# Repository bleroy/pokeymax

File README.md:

# This repo is somewhat obsolete

I created this repo when Foft first released his design of the PokeyMax 4 board publicly.
I did so at the time because the design was still in Eagle format and somewhat difficult to keep track of.
I took the design, imported it to KiCad and published it here as a git repo.
I also took a stab at redesigning the board to bring the price down as much as possible (that's the 4s version of the board).

A lot has happened since.
Foft released multiple revisions of the board and HDL files, and quite a few people have built their own boards.
He's now using KiCad, so no more Eagle.
He also started working on a 4.5 revision as well as on several new designs, including the PokeyMin that uses a smaller FPGA version and resistors instead of level shifters.
That last design pretty much makes 4s obsolete and little more than a curiosity. For me, it was a nice exercise in designing such a small board.

In other words, nobody except maybe me should use the files on this repo. Instead, head over to Foft's site and download the latest files from there:
http://www.64kib.com/atarixlfpga_svn/trunk/atari_800xl/atari_chips/hardware/

# PokeyMax 4

Foft's public designs for PokeyMax.

Pokeys are getting rare and expensive. FPGA alternatives exist but are also expensive. Foft, the author of PokeyMax, has very generously made his designs public on [the AtariAge forums](https://forums.atariage.com/topic/364870-pokeymax-v4-bring-up-thread/).
With his permission, I'm publishing his latest iteration on PokeyMax, version 4, which is a 2-layer version with all components on the top side. This should be easier to produce at a lower cost than the previous versions. I've also imported the project in KiCad from the original Eagle files.

Foft has not specified a license for his work, but attribution should be maintained. This is his design, reproduced here under his permission.

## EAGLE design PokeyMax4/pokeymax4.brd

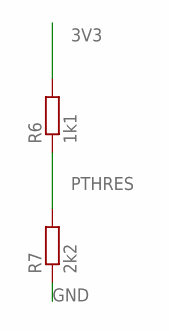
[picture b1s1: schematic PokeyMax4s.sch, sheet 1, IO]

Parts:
R6: 1k1; R0402
R7: 2k2; R0402

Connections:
3V3: R6.2; also elsewhere on the board
GND: R7.1; also elsewhere on the board
PTHRES: R6.1, R7.2; also elsewhere on the board

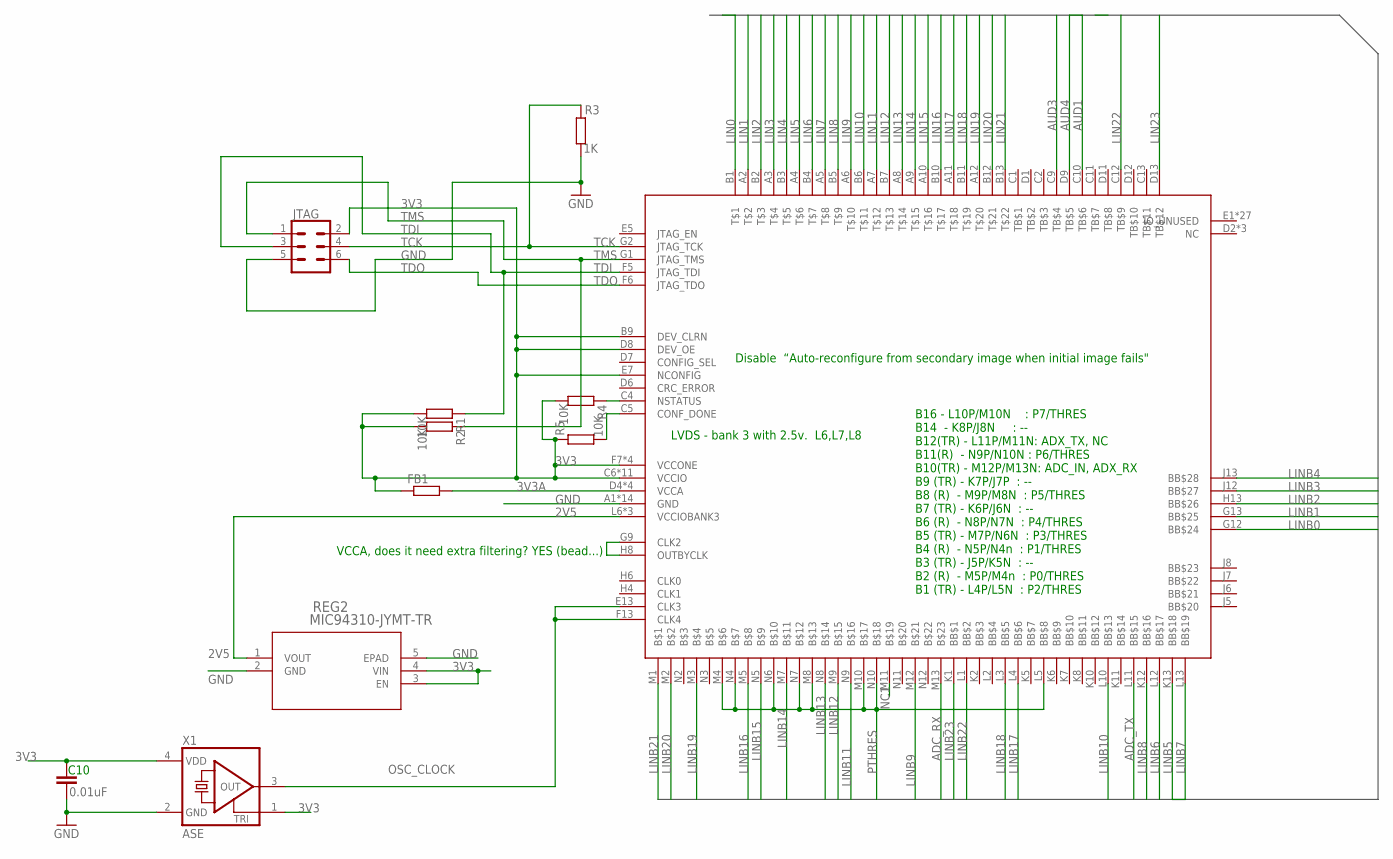
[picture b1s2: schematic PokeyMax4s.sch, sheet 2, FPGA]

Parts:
C10: 0.01uF; C0402
FB1: R-EU_R0402; R0402
JTAG: CONN_03X2LOCK; 2X3_LOCK
R1, R2, R4, R5: 10K; R0402
R3: 1K; R0402
REG2: MIC94310-JYMT-TR; TDFN4_1P2X1P6_MCH
U3: MAX10; U169SMALL
X1: ASE

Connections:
2V5: REG2.1 (VOUT), U3.L6 (VCCIOBANK3), U3.L7 (VCCIOBANK3), U3.L8 (VCCIOBANK3); also elsewhere on the board
3V3: C10.1, FB1.1, JTAG.2, R1.2, R2.2, R4.2, R5.1, REG2.3 (EN), REG2.4 (VIN), U3.B9 (DEV_CLRN), U3.C6 (VCCIO), U3.C7 (VCCIO), U3.C8 (VCCIO), U3.D8 (DEV_OE), U3.E7 (NCONFIG), U3.F2 (VCCIO), U3.F7 (VCCONE), U3.F11 (VCCIO), U3.G3 (VCCIO), U3.G6 (VCCONE), U3.G8 (VCCONE), U3.G11 (VCCIO), U3.H7 (VCCONE), U3.H11 (VCCIO), U3.J3 (VCCIO), U3.J11 (VCCIO), U3.K3 (VCCIO), X1.1 (TRI), X1.4 (VDD); also elsewhere on the board
3V3A: FB1.2, U3.D4 (VCCA), U3.D10 (VCCA), U3.K4 (VCCA), U3.K9 (VCCA); also elsewhere on the board
ADC_RX: U3.M13; also elsewhere on the board
ADC_TX: U3.L11 (BB$15); also elsewhere on the board
AUD1: U3.C10 (TB$6); also elsewhere on the board
AUD3: U3.C9 (TB$4); also elsewhere on the board
AUD4: U3.D9 (TB$5); also elsewhere on the board
CONF_DONE: R5.2, U3.C5 (CONF_DONE)
FAKE_CLK: U3.G9 (CLK2), U3.H8 (OUTBYCLK)
GND: C10.2, JTAG.5, R3.2, REG2.2 (GND), REG2.5 (EPAD), U3.A1 (GND), U3.A13 (GND), U3.B8 (GND), U3.C3 (GND), U3.D5 (GND), U3.E11 (GND), U3.F3 (GND), U3.G7 (GND), U3.H12 (GND), U3.J4 (GND), U3.L9 (GND), U3.M6 (GND), U3.N1 (GND), U3.N13 (GND), X1.2 (GND); also elsewhere on the board
LIN0: U3.B1; also elsewhere on the board
LIN1: U3.A2; also elsewhere on the board
LIN2: U3.B2; also elsewhere on the board
LIN3: U3.A3; also elsewhere on the board
LIN4: U3.B3; also elsewhere on the board
LIN5: U3.A4; also elsewhere on the board
LIN6: U3.B4; also elsewhere on the board
LIN7: U3.A5; also elsewhere on the board
LIN8: U3.B5; also elsewhere on the board
LIN9: U3.A6; also elsewhere on the board
LIN10: U3.B6; also elsewhere on the board
LIN11: U3.A7; also elsewhere on the board
LIN12: U3.B7; also elsewhere on the board
LIN13: U3.A8; also elsewhere on the board
LIN14: U3.A9; also elsewhere on the board
LIN15: U3.A10; also elsewhere on the board
LIN16: U3.B10; also elsewhere on the board
LIN17: U3.A11; also elsewhere on the board
LIN18: U3.B11; also elsewhere on the board
LIN19: U3.A12; also elsewhere on the board
LIN20: U3.B12; also elsewhere on the board
LIN21: U3.B13; also elsewhere on the board
LIN22: U3.C12 (TB$9); also elsewhere on the board
LIN23: U3.D13 (TB$12); also elsewhere on the board
LINB0: U3.G12 (BB$24); also elsewhere on the board
LINB1: U3.G13 (BB$25); also elsewhere on the board
LINB2: U3.H13 (BB$26); also elsewhere on the board
LINB3: U3.J12 (BB$27); also elsewhere on the board
LINB4: U3.J13 (BB$28); also elsewhere on the board
LINB5: U3.K13 (BB$18); also elsewhere on the board
LINB6: U3.L12 (BB$17); also elsewhere on the board
LINB7: U3.L13 (BB$19); also elsewhere on the board
LINB8: U3.K12 (BB$16); also elsewhere on the board
LINB9: U3.M12; also elsewhere on the board
LINB10: U3.L10 (BB$13); also elsewhere on the board
LINB11: U3.N9; also elsewhere on the board
LINB12: U3.M9; also elsewhere on the board
LINB13: U3.N8; also elsewhere on the board
LINB14: U3.M7; also elsewhere on the board
LINB15: U3.N5; also elsewhere on the board
LINB16: U3.M5; also elsewhere on the board
LINB17: U3.L4 (BB$6); also elsewhere on the board
LINB18: U3.L3 (BB$5); also elsewhere on the board
LINB19: U3.M3; also elsewhere on the board
LINB20: U3.M2; also elsewhere on the board
LINB21: U3.M1; also elsewhere on the board
LINB22: U3.L1 (BB$2); also elsewhere on the board
LINB23: U3.K1 (BB$1); also elsewhere on the board
NC1: U3.M11
NSTATUS: R4.1, U3.C4 (NSTATUS)
OSC_CLOCK: U3.E13 (CLK3), U3.F13 (CLK4), X1.3 (OUT)
PTHRES: U3.L5 (BB$8), U3.M4, U3.M8, U3.M10, U3.N4, U3.N6, U3.N7, U3.N10; also elsewhere on the board
TCK: JTAG.4, R3.1, U3.G2 (JTAG_TCK)
TDI: JTAG.3, R1.1, U3.F5 (JTAG_TDI)
TDO: JTAG.6, U3.F6 (JTAG_TDO)
TMS: JTAG.1, R2.1, U3.G1 (JTAG_TMS)

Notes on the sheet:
VCCA, does it need extra filtering? YES (bead...)
Disable “Auto-reconfigure from secondary image when initial image fails"
LVDS - bank 3 with 2.5v. L6,L7,L8
B16 - L10P/M10N : P7/THRES B14 - K8P/J8N : -- B12(TR) - L11P/M11N: ADX_TX, NC B11(R) - N9P/N10N : P6/THRES B10(TR) - M12P/M13N: ADC_IN, ADX_RX B9 (TR) - K7P/J7P : -- B8 (R) - M9P/M8N : P5/THRES B7 (TR) - K6P/J6N : -- B6 (R) - N8P/N7N : P4/THRES B5 (TR) - M7P/N6N : P3/THRES B4 (R) - N5P/N4n : P1/THR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

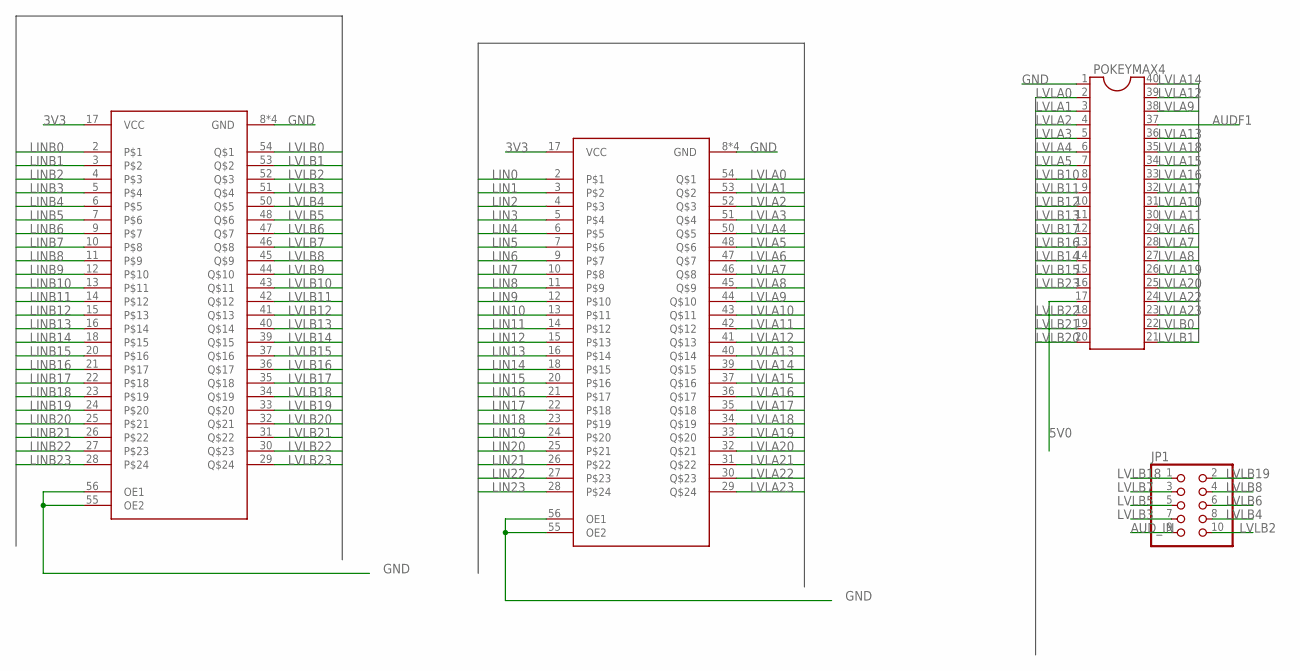
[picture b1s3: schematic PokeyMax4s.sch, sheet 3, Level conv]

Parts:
JP1: PINHD-2X5; 2X05
POKEYMAX4: DIL40
U2, U4: SN74CB3T16211SM; 56TVSOP_SMALL

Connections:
3V3: U2.17 (VCC), U4.17 (VCC); also elsewhere on the board
5V0: POKEYMAX4.17; also elsewhere on the board
AUDF1: POKEYMAX4.37; also elsewhere on the board
AUD_IN: JP1.9; also elsewhere on the board
GND: POKEYMAX4.1, U2.8 (GND), U2.19 (GND), U2.38 (GND), U2.49 (GND), U2.55 (OE2), U2.56 (OE1), U4.8 (GND), U4.19 (GND), U4.38 (GND), U4.49 (GND), U4.55 (OE2), U4.56 (OE1); also elsewhere on the board
LIN0: U2.2; also elsewhere on the board
LIN1: U2.3; also elsewhere on the board
LIN2: U2.4; also elsewhere on the board
LIN3: U2.5; also elsewhere on the board
LIN4: U2.6; also elsewhere on the board
LIN5: U2.7; also elsewhere on the board
LIN6: U2.9; also elsewhere on the board
LIN7: U2.10; also elsewhere on the board
LIN8: U2.11; also elsewhere on the board
LIN9: U2.12; also elsewhere on the board
LIN10: U2.13; also elsewhere on the board
LIN11: U2.14; also elsewhere on the board
LIN12: U2.15; also elsewhere on the board
LIN13: U2.16; also elsewhere on the board
LIN14: U2.18; also elsewhere on the board
LIN15: U2.20; also elsewhere on the board
LIN16: U2.21; also elsewhere on the board
LIN17: U2.22; also elsewhere on the board
LIN18: U2.23; also elsewhere on the board
LIN19: U2.24; also elsewhere on the board
LIN20: U2.25; also elsewhere on the board
LIN21: U2.26; also elsewhere on the board
LIN22: U2.27; also elsewhere on the board
LIN23: U2.28; also elsewhere on the board
LINB0: U4.2; also elsewhere on the board
LINB1: U4.3; also elsewhere on the board
LINB2: U4.4; also elsewhere on the board
LINB3: U4.5; also elsewhere on the board
LINB4: U4.6; also elsewhere on the board
LINB5: U4.7; also elsewhere on the board
LINB6: U4.9; also elsewhere on the board
LINB7: U4.10; also elsewhere on the board
LINB8: U4.11; also elsewhere on the board
LINB9: U4.12; also elsewhere on the board
LINB10: U4.13; also elsewhere on the board
LINB11: U4.14; also elsewhere on the board
LINB12: U4.15; also elsewhere on the board
LINB13: U4.16; also elsewhere on the board
LINB14: U4.18; also elsewhere on the board
LINB15: U4.20; also elsewhere on the board
LINB16: U4.21; also elsewhere on the board
LINB17: U4.22; also elsewhere on the board
LINB18: U4.23; also elsewhere on the board
LINB19: U4.24; also elsewhere on the board
LINB20: U4.25; also elsewhere on the board
LINB21: U4.26; also elsewhere on the board
LINB22: U4.27; also elsewhere on the board
LINB23: U4.28; also elsewhere on the board
LVLA0: POKEYMAX4.2, U2.54
LVLA1: POKEYMAX4.3, U2.53
LVLA2: POKEYMAX4.4, U2.52
LVLA3: POKEYMAX4.5, U2.51
LVLA4: POKEYMAX4.6, U2.50
LVLA5: POKEYMAX4.7, U2.48
LVLA6: POKEYMAX4.29, U2.47
LVLA7: POKEYMAX4.28, U2.46
LVLA8: POKEYMAX4.27, U2.45
LVLA9: POKEYMAX4.38, U2.44
LVLA10: POKEYMAX4.31, U2.43
LVLA11: POKEYMAX4.30, U2.42
LVLA12: POKEYMAX4.39, U2.41
LVLA13: POKEYMAX4.36, U2.40
LVLA14: POKEYMAX4.40, U2.39
LVLA15: POKEYMAX4.34, U2.37
LVLA16: POKEYMAX4.33, U2.36
LVLA17: POKEYMAX4.32, U2.35
LVLA18: POKEYMAX4.35, U2.34
LVLA19: POKEYMAX4.26, U2.33
LVLA20: POKEYMAX4.25, U2.32
LVLA21: U2.31; also elsewhere on the board
LVLA22: POKEYMAX4.24, U2.30
LVLA23: POKEYMAX4.23, U2.29
LVLB0: POKEYMAX4.22, U4.54
LVLB1: POKEYMAX4.21, U4.53
LVLB2: JP1.10, U4.52
LVLB3: JP1.7, U4.51
LVLB4: JP1.8, U4.50
LVLB5: JP1.5, U4.48
LVLB6: JP1.6, U4.47
LVLB7: JP1.3, U4.46
LVLB8: JP1.4, U4.45
LVLB9: U4.44; also elsewhere on the board
LVLB10: POKEYMAX4.8, U4.43
LVLB11: POKEYMAX4.9, U4.42
LVLB12: POKEYMAX4.10, U4.41
LVLB13: POKEYMAX4.11, U4.40
LVLB14: POKEYMAX4.14, U4.39
LVLB15: POKEYMAX4.15, U4.37
LVLB16: POKEYMAX4.13, U4.36
LVLB17: POKEYMAX4.12, U4.35
LVLB18: JP1.1, U4.34
LVLB19: JP1.2, U4.33
LVLB20: POKEYMAX4.20, U4.32
LVLB21: POKEYMAX4.19, U4.31
LVLB22: POKEYMAX4.18, U4.30
LVLB23: POKEYMAX4.16, U4.29

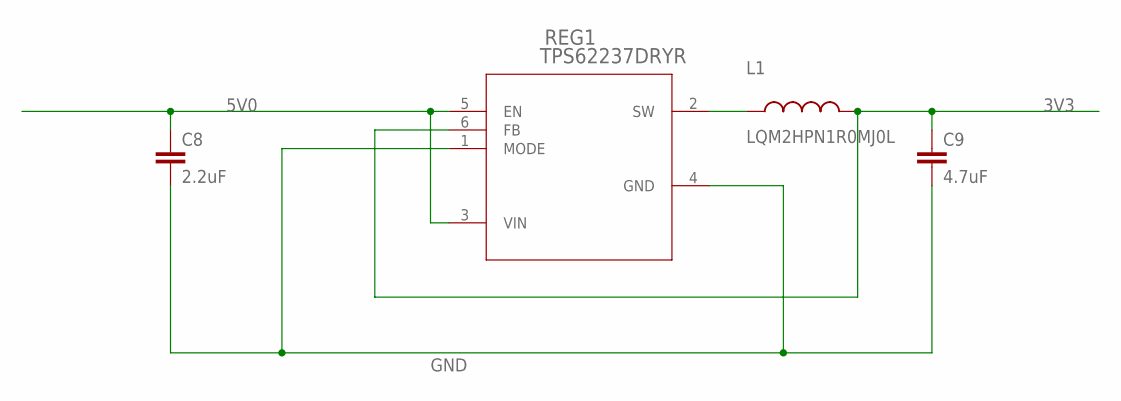
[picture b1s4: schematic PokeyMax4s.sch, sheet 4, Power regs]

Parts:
C8: 2.2uF; C0402
C9: 4.7uF; C0402
L1: LQM2HPN1R0MJ0L; INDC1008X04
REG1: TPS62237DRYR; DRY6

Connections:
3V3: C9.1, L1.2, REG1.6 (FB); also elsewhere on the board
5V0: C8.1, REG1.3 (VIN), REG1.5 (EN); also elsewhere on the board
GND: C8.2, C9.2, REG1.1 (MODE), REG1.4 (GND); also elsewhere on the board
unnamed: L1.1, REG1.2 (SW)

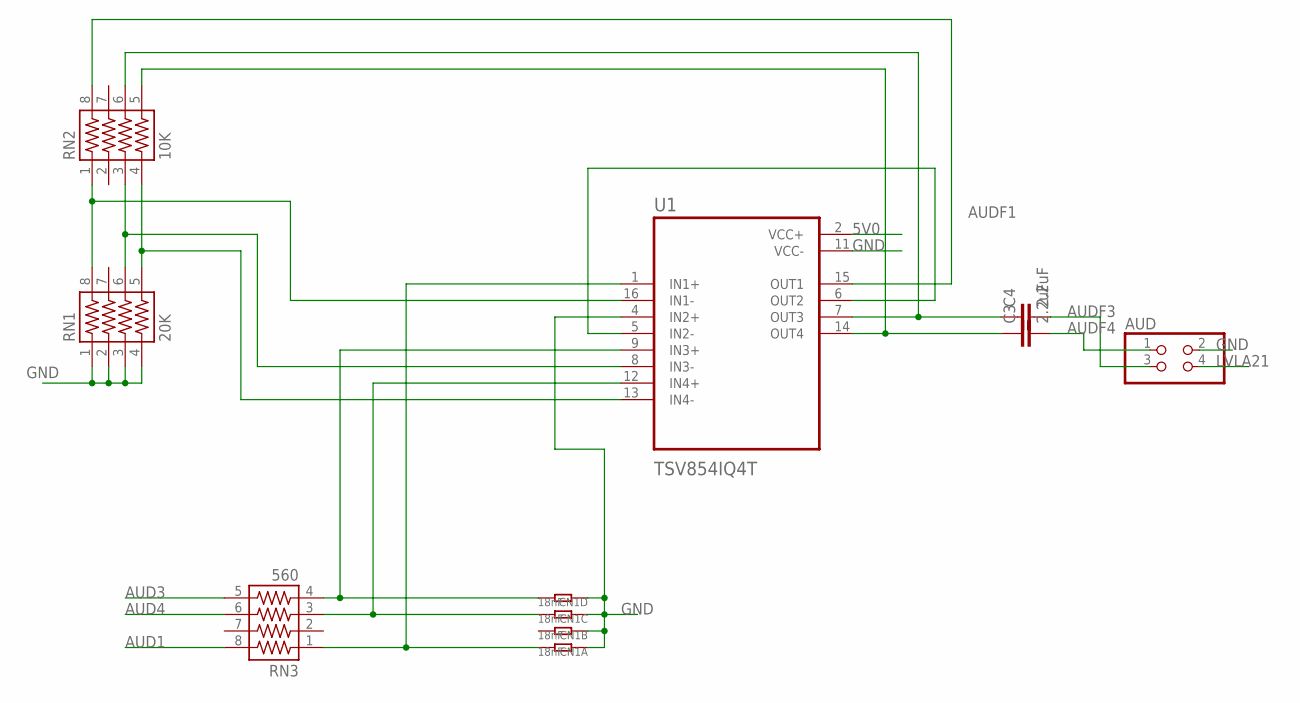
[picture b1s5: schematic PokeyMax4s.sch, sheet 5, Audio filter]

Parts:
AUD: PINHD-2X2; 2X02
C3, C4: 2.2uF; C0402
CN1: 18nF; R1206-8
RN1: 20K; 741-8
RN2: 10K; 741-8
RN3: 560; 741-8
U1: TSV854IQ4T; QFN50P300X300X100-16N

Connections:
5V0: U1.2 (VCC+); also elsewhere on the board
AMPIN1M: RN1.8, RN2.1, U1.16 (IN1-)
AMPIN1P: CN1.8 (2), RN3.1, U1.1 (IN1+)
AMPIN3M: RN1.6, RN2.3, U1.8 (IN3-)
AMPIN3P: CN1.5 (2), RN3.4, U1.9 (IN3+)
AMPIN4P: CN1.6 (2), RN3.3, U1.12 (IN4+)
AUD1: RN3.8; also elsewhere on the board
AUD3: RN3.5; also elsewhere on the board
AUD4: RN3.6; also elsewhere on the board
AUDF1: RN2.8, U1.15 (OUT1); also elsewhere on the board
AUDF2: U1.5 (IN2-), U1.6 (OUT2)
AUDF3: AUD.3, C4.2
AUDF4: AUD.1, C3.2
GND: AUD.2, CN1.1, CN1.2 (1), CN1.3 (1), CN1.4 (1), RN1.1, RN1.2, RN1.3, RN1.4, U1.4 (IN2+), U1.11 (VCC-); also elsewhere on the board
LVLA21: AUD.4; also elsewhere on the board
unnamed: C3.1, RN2.5, U1.14 (OUT4)
unnamed: C4.1, RN2.6, U1.7 (OUT3)
unnamed: RN1.5, RN2.4, U1.13 (IN4-)

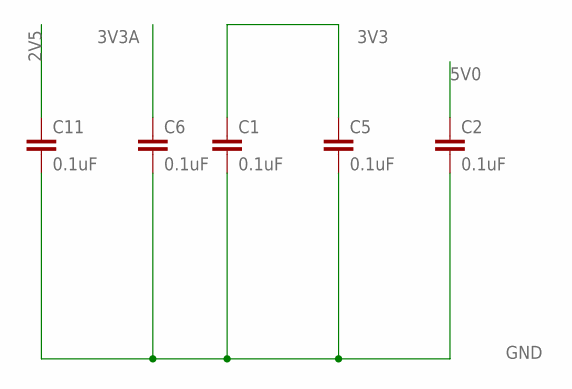
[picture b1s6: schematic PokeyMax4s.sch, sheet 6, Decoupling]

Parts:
C1, C2, C5, C6, C11: 0.1uF; C0402

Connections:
2V5: C11.1; also elsewhere on the board
3V3: C1.1, C5.1; also elsewhere on the board
3V3A: C6.1; also elsewhere on the board
5V0: C2.1; also elsewhere on the board
GND: C1.2, C2.2, C5.2, C6.2, C11.2; also elsewhere on the board

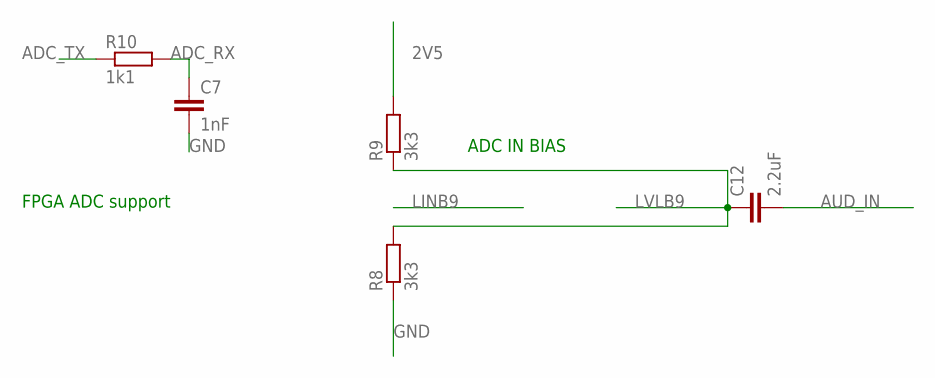
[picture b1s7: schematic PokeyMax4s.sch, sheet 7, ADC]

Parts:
C7: 1nF; C0402
C12: 2.2uF; C0402
R8, R9: 3k3; R0402
R10: 1k1; R0402

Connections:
2V5: R9.2; also elsewhere on the board
ADC_RX: C7.1, R10.2; also elsewhere on the board
ADC_TX: R10.1; also elsewhere on the board
AUD_IN: C12.2; also elsewhere on the board
GND: C7.2, R8.1; also elsewhere on the board
LVLB9: C12.1, R8.2, R9.1; also elsewhere on the board

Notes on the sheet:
ADC IN BIAS
FPGA ADC support

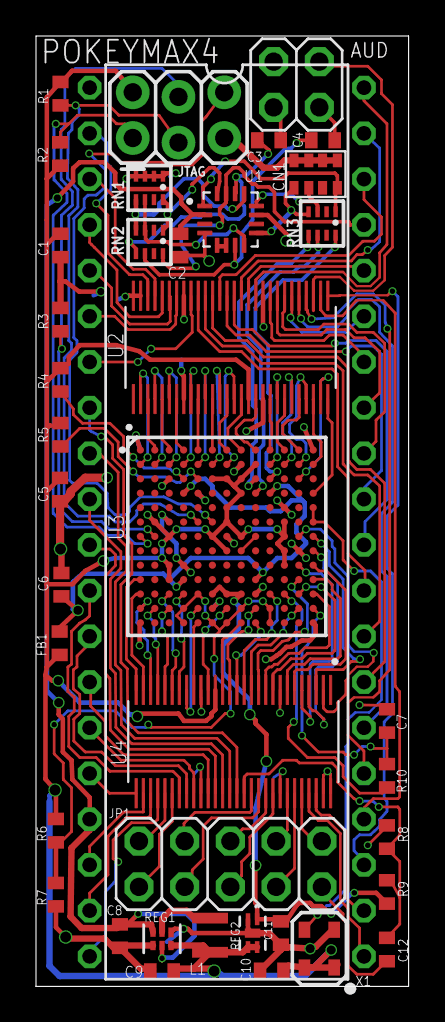
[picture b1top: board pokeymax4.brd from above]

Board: 2 copper layers, 20.7 x 52.8 mm, 39 parts (0 on the bottom side), 129 nets.

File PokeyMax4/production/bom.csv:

Designator,Footprint,Quantity,Value,LCSC Part #
AUD0,2X02,1,,
"C1, C11, C2, C5, C6",C0402,5,0.1uF,
C10,C0402,1,0.01uF,
"C12, C3, C4, C8",C0402,4,2.2uF,
C7,C0402,1,1nF,
C9,C0402,1,4.7uF,
CN1,R1206-8,1,18nF,
FB1,R0402,1,,
JP1,2X05,1,,
JTAG0,2X3_LOCK,1,,
L1,INDC1008X04,1,LQM2HPN1R0MJ0L,
POKEYMAX4,DIL40,1,,
"R1, R2, R4, R5",R0402,4,10K,
"R10, R6",R0402,2,1k1,
R3,R0402,1,1K,
R7,R0402,1,2k2,
"R8, R9",R0402,2,3k3,
REG1,DRY6,1,TPS62237DRYR,
REG2,TDFN4_1P2X1P6_MCH,1,MIC94310-JYMT-TR,
RN1,741-8,1,20K,
RN2,741-8,1,10K,
RN3,741-8,1,560,
U1,QFN50P300X300X100-16N,1,TSV854IQ4T,
"U2, U4",56TVSOP_SMALL,2,SN74CB3T16211SM,
U3,U169SMALL,1,MAX10,
X1,ASE,1,ASE,

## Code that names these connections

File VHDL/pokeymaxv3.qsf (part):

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set_global_assignment -name DEVICE_FILTER_PIN_COUNT 169
set_global_assignment -name DEVICE_FILTER_SPEED_GRADE 8
set_global_assignment -name ERROR_CHECK_FREQUENCY_DIVISOR 256
set_location_assignment PIN_B3 -to PHI2   #B3,LVLA4,PHI
set_location_assignment PIN_A3 -to D[7]   #A3,LVLA3,D7
set_location_assignment PIN_B2 -to D[6]   #B2,LVLA2,D6
set_location_assignment PIN_A2 -to D[5]   #A2,LVLA1,LVL5,D5
set_location_assignment PIN_B1 -to D[4]   #B1,LVLA0,D4
set_location_assignment PIN_A4 -to D[3]   #A4,LVLA5,D3
set_location_assignment PIN_A11 -to D[2]  #A11,LVLA17,D2
set_location_assignment PIN_B10 -to D[1]  #B10,LVLA16,D1
set_location_assignment PIN_A10 -to D[0]  #A10,LVLA15,D0
set_location_assignment PIN_A5 -to CS0_N  #A5,LVLA,CS0_N
set_location_assignment PIN_B6 -to CS1    #B6,LVLA10,CS1
set_location_assignment PIN_B4 -to IRQ    #B4,LVLA6,IRQ_N
set_location_assignment PIN_B5 -to W_N    #B5,LVLA8,RW
set_location_assignment PIN_A7 -to SID    #A7,LVLA11,SID
set_location_assignment PIN_A9 -to SOD    #A9,LVLA14,SOD
set_location_assignment PIN_A8 -to ACLK   #A8,LVLA13,ACLK
set_location_assignment PIN_B7 -to BCLK   #B7,LVLA12,BCLK
set_location_assignment PIN_B11 -to A[0]  #B11,LVLA18,A0
set_location_assignment PIN_B12 -to A[1]  #B12,LVLA20,A1
set_location_assignment PIN_C13 -to A[2]   #C13,LVLA22,A2
set_location_assignment PIN_A6 -to A[3]   #A6,LVLA9,A3

set_location_assignment PIN_N2 -to PADDLE[5]  #11=N2 POT7 p5
set_location_assignment PIN_N3 -to PADDLE[1]  #15=N3 POT6 p1
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set_location_assignment PIN_N9 -to PADDLE[2]  #12=N9 POT0 p2
set_location_assignment PIN_M2 -to POTRESET_N  #POTRESET - M2

set_location_assignment PIN_C11 -to AUD[1] #AUD1 - C11
set_location_assignment PIN_D11 -to AUD[3] #AUD3 - D11
set_location_assignment PIN_C12 -to AUD[2] #AUD2 - C12
set_location_assignment PIN_D12 -to AUD[4] #AUD4 - D12

set_location_assignment PIN_M3 -to IOX_RST   #IOX_RST - M3
set_location_assignment PIN_M4 -to IOX_SDA   #IOX_SDA - M4
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set_location_assignment PIN_H6 -to CLK0      #CLK0 - H6
set_location_assignment PIN_H4 -to CLK1      #CLK1 - H4

set_location_assignment PIN_A12 -to EXT[1] #A12,LVLA19,EXT3
set_location_assignment PIN_B13 -to EXT[2] #B13,LVLA21,EXT2
set_location_assignment PIN_D13 -to EXT[3] #D13,LVLA23,EXT1
set_location_assignment PIN_M9 -to EXT[4] #LVLB0  EXT4  - M9
set_location_assignment PIN_M10 -to EXT[5] #LVLB1  EXT5  - M10
set_location_assignment PIN_N10 -to EXT[6] #LVLB2  EXT6  - N10
set_location_assignment PIN_M11 -to EXT[7] #LVLB3  EXT7  - M11
set_location_assignment PIN_N11 -to EXT[8] #LVLB4  EXT8  - N11
set_location_assignment PIN_M12 -to EXT[9] #LVLB5  EXT9  - M12
set_location_assignment PIN_N12 -to EXT[10] #LVLB6  EXT10 - N12
set_location_assignment PIN_M13 -to EXT[11] #LVLB7  EXT11 - M13

set_instance_assignment -name WEAK_PULL_UP_RESISTOR ON -to IOX_RST
set_instance_assignment -name WEAK_PULL_UP_RESISTOR ON -to IOX_INT
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
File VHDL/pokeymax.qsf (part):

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set_global_assignment -name DEVICE_FILTER_PIN_COUNT 169
set_global_assignment -name DEVICE_FILTER_SPEED_GRADE 8
set_global_assignment -name ERROR_CHECK_FREQUENCY_DIVISOR 256
set_location_assignment PIN_B1 -to PHI2    #B1,LIN0,LVL8,PHI
set_location_assignment PIN_A2 -to D[7]   #A2,LIN1,LVL7,D7
set_location_assignment PIN_B2 -to D[6]   #B2,LIN2,LVL6,D6
set_location_assignment PIN_A3 -to D[5]   #A3,LIN3,LVL5,D5
set_location_assignment PIN_B3 -to D[4]   #B3,LIN4,LVL4,D4
set_location_assignment PIN_A4 -to D[3]   #A4,LIN5,LVL3,D3
set_location_assignment PIN_B4 -to CS0_N  #B4,LIN6,LVL21,CS0_N
set_location_assignment PIN_A5 -to CS1    #A5,LIN7,LVL9,CS1
set_location_assignment PIN_B5 -to IRQ    #B5,LIN8,LVL14,IRQ_N
set_location_assignment PIN_A6 -to W_N    #A6,LIN9,LVL15,RW
set_location_assignment PIN_B6 -to SOD    #B6,LIN10,LVL13,SOD
set_location_assignment PIN_A7 -to ACLK   #A7,LIN11,LVL12,ACLK
set_location_assignment PIN_B7 -to BCLK   #B7,LIN12,LVL11,BCLK
set_location_assignment PIN_A8 -to A[3]   #A8,LIN13,LVL16,A3
set_location_assignment PIN_A9 -to SID    #A9,LIN14,LVL10,SID
set_location_assignment PIN_A10 -to D[2]  #A10,LIN15,LVL2,D2
set_location_assignment PIN_B10 -to D[1]  #B10,LIN16,LVL1,D1
set_location_assignment PIN_A11 -to D[0]  #A11,LIN17,LVL0,D0
set_location_assignment PIN_B11 -to A[0]  #B11,LIN18,LVL19,A0
set_location_assignment PIN_A12 -to EXT[1] #A12,LIN19,LVL23,EXT3
set_location_assignment PIN_B12 -to A[1]  #B12,LIN20,LVL18,A1
set_location_assignment PIN_B13 -to EXT[2] #B13,LIN21,LVL22,EXT2
set_location_assignment PIN_C11 -to AUD[1] #C11,AUD1,AUDF1,AUD
set_location_assignment PIN_D11 -to AUD[3] #D11,AUD2,AUDF4,AUDEXT2
set_location_assignment PIN_C12 -to AUD[4] #C12,AUD3,AUDF2,AUDEXT3
set_location_assignment PIN_D12 -to AUD[2] #D12,AUD4,AUDF3,AUDEXT1
set_location_assignment PIN_C13 -to A[2]   #C13,LIN22,LVL17,A2
set_location_assignment PIN_D13 -to EXT[3] #D13,LIN23,LVL20,EXT1
set_location_assignment PIN_N2 -to PADDLE[5]  #N2,PIN3,POT7,P5
set_location_assignment PIN_N3 -to PADDLE[1]  #N3,PIN2,POT6,P1
set_location_assignment PIN_N4 -to PADDLE[4]  #N4,PIN0,POT5,P4
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
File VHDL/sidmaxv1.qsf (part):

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set_global_assignment -name DEVICE_FILTER_SPEED_GRADE 8
set_global_assignment -name ERROR_CHECK_FREQUENCY_DIVISOR 256

set_location_assignment PIN_B1 -to PHI2 #B1,LIN0,P6,PHI
set_location_assignment PIN_A2 -to RST_N #A2,LIN1,P5,RST
set_location_assignment PIN_B2 -to CS_N #B2,LIN2,P8,CS_N
set_location_assignment PIN_A3 -to W_N #A3,LIN3,P7,RW_N
set_location_assignment PIN_B3 -to A[0] #B3,LIN4,P9,A0
set_location_assignment PIN_A4 -to A[1] #A4,LIN5,P10,A1
set_location_assignment PIN_B4 -to A[2] #B4,LIN6,P11,A2
set_location_assignment PIN_A5 -to A[3] #A5,LIN7,P12,A3
set_location_assignment PIN_B5 -to A[4] #B5,LIN8,P13,A4
set_location_assignment PIN_A6 -to D[0] #A6,LIN9,P15,D0
set_location_assignment PIN_B6 -to D[1] #B6,LIN10,P16,D1
set_location_assignment PIN_A7 -to D[2] #A7,LIN11,P17,D2
set_location_assignment PIN_B7 -to D[3] #B7,LIN12,P18,D3
set_location_assignment PIN_A8 -to D[4] #A8,LIN13,P19,D4
set_location_assignment PIN_A9 -to D[7] #A9,LIN14,P22,D7
set_location_assignment PIN_A10 -to D[6] #A10,LIN15,P21,D6
set_location_assignment PIN_B10 -to D[5] #B10,LIN16,P20,D5
set_location_assignment PIN_A11 -to EXT[3] #A11,LIN17,EXT1
set_location_assignment PIN_B11 -to EXT[2] #B11,LIN18,EXT2
set_location_assignment PIN_A12 -to EXT[1] #A12,LIN19,EXT3
set_location_assignment PIN_B12 -to EXT[4] #B12,LIN20,EXT4

set_location_assignment PIN_C9 -to AUDIO_LEFT ###C9,AUD3,AUDIO_LEFT
set_location_assignment PIN_D9 -to AUDIO_RIGHT ###D9,AUD4,AUDIO_RIGHT
set_location_assignment PIN_C10 -to AUDIO_INT ###C10,AUD1,AUDIO_INT

set_location_assignment PIN_L10 -to EXT_IN_p #L10,LIN22,P26,EXT_IN
set_location_assignment PIN_M10 -to EXT_IN_n #ADC_RX #M10,ADC_RX,
set_location_assignment PIN_K8 -to ADC_TX_p #K8,ADC_TX,
set_location_assignment PIN_J8 -to ADC_TX_n #K8,ADC_TX,

set_location_assignment PIN_K7 -to POTY_p #K7,LIN21,P23,POTY
set_location_assignment PIN_J7 -to POTY_n #K7,LIN21,P23,POTY
set_location_assignment PIN_K6 -to POTY_RESET #K6,POTY_RESET,
#set_location_assignment PIN_J6 -to POTY_RESET(n) ###J6,NC3,
set_location_assignment PIN_L11 -to POTX_p #L11,LIN23,P24,POTX
set_location_assignment PIN_M11 -to POTX_n #L11,LIN23,P24,POTX
set_location_assignment PIN_M12 -to POTX_RESET #M12,POTX_RESET,
#set_location_assignment PIN_M13 -to POTX_RESET(n) ###M13,NC2,

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
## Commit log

2024-04-17 Initial push of KiCad import of PokeyMax 4 files
2024-04-18 Add VHDL
2024-08-10 Update the v4 board
2024-08-18 Updates for JLCPCB fabrication and parts library
2024-08-21 Final adjustements to production files for JLC
2024-08-21 Nothing really
2024-08-22 Update BOM from 0402 to 0603 where relevant
2024-08-25 Pokeymax 4s WIP
2024-08-25 Complete routing of Pokeymax 4s
    Removed backup dirs from repo
2024-08-25 PokeyMax 4s silkscreen
2024-08-25 PokeyMax 4s fabrication files
2024-08-27 Add A4 to PokeyMax 4s
    Reroute accordingly
2024-08-28 Last adjustments to 4s
2024-08-28 Fix typo on 4s board
2025-06-21 Fix LIN22 to AUD1 erroneous connection
2025-06-21 Bump rev number to 1.1
2025-06-21 Rebuild prod files with rev number

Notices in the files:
VHDL/pokeymax.qsf:
Copyright (C) 2017  Intel Corporation. All rights reserved.
parts and their libraries:
resistor-array: Copyright (C) 2008, Bob Starr
SparkFun-Connectors: Licensing: Creative Commons ShareAlike 4.0 International - https://creativecommons.org/licenses/by-sa/4.0
COPYRIGHT: Copyright (C) 2018 Accelerated Designs. All rights reserved
